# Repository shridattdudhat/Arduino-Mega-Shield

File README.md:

# Arduino-Mega-Shield
Arduino Mega Shield

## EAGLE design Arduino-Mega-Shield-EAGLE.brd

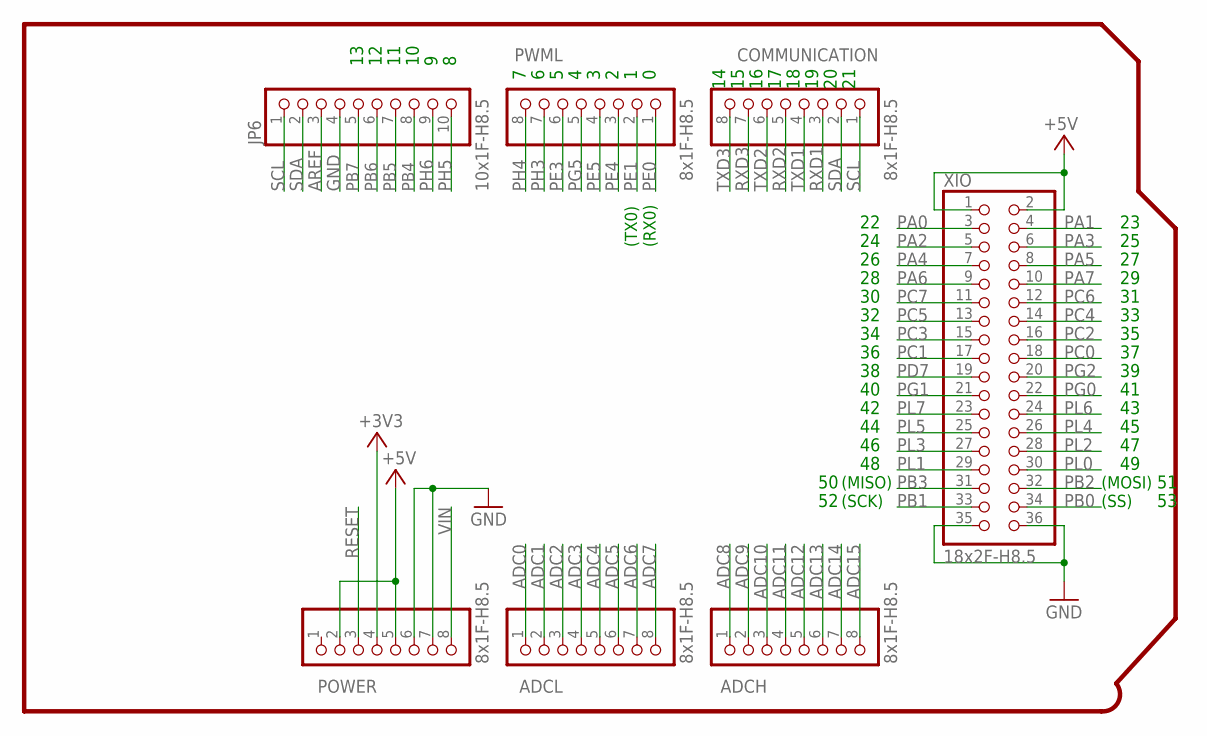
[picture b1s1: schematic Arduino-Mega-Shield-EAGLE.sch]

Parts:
ADCH: 8x1F-H8.5; 1X08
ADCL: 8x1F-H8.5; 1X08
COMMUNICATION: 8x1F-H8.5; 1X08
JP6: 10x1F-H8.5; 1X10
POWER: 8x1F-H8.5; 1X08
PWML: 8x1F-H8.5; 1X08
XIO: 18x2F-H8.5; 2X18

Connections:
+3V3: POWER.4
+5V: POWER.2, POWER.5, XIO.1, XIO.2
ADC0: ADCL.1
ADC1: ADCL.2
ADC2: ADCL.3
ADC3: ADCL.4
ADC4: ADCL.5
ADC5: ADCL.6
ADC6: ADCL.7
ADC7: ADCL.8
ADC8: ADCH.1
ADC9: ADCH.2
ADC10: ADCH.3
ADC11: ADCH.4
ADC12: ADCH.5
ADC13: ADCH.6
ADC14: ADCH.7
ADC15: ADCH.8
AREF: JP6.3
GND: JP6.4, POWER.6, POWER.7, XIO.35, XIO.36
PA0: XIO.3
PA1: XIO.4
PA2: XIO.5
PA3: XIO.6
PA4: XIO.7
PA5: XIO.8
PA6: XIO.9
PA7: XIO.10
PB0: XIO.34
PB1: XIO.33
PB2: XIO.32
PB3: XIO.31
PB4: JP6.8
PB5: JP6.7
PB6: JP6.6
PB7: JP6.5
PC0: XIO.18
PC1: XIO.17
PC2: XIO.16
PC3: XIO.15
PC4: XIO.14
PC5: XIO.13
PC6: XIO.12
PC7: XIO.11
PD7: XIO.19
PE0: PWML.1
PE1: PWML.2
PE3: PWML.6
PE4: PWML.3
PE5: PWML.4
PG0: XIO.22
PG1: XIO.21
PG2: XIO.20
PG5: PWML.5
PH3: PWML.7
PH4: PWML.8
PH5: JP6.10
PH6: JP6.9
PL0: XIO.30
PL1: XIO.29
PL2: XIO.28
PL3: XIO.27
PL4: XIO.26
PL5: XIO.25
PL6: XIO.24
PL7: XIO.23
RESET: POWER.3
RXD1: COMMUNICATION.3
RXD2: COMMUNICATION.5
RXD3: COMMUNICATION.7
SCL: COMMUNICATION.1, JP6.1
SDA: COMMUNICATION.2, JP6.2
TXD1: COMMUNICATION.4
TXD2: COMMUNICATION.6
TXD3: COMMUNICATION.8
VIN: POWER.8

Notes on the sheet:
(TX0)
(RX0)
(SS)
(MOSI)
(SCK)
(MISO)

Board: 2 copper layers, 7 parts (0 on the bottom side), 4 nets, no tracks yet.

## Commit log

2018-12-30 PCB and SCH file of Shield | ini Commit
